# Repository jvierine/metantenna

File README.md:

# Open antenna designs

**TL;DR:** Open-source antenna hardware designs aimed at high performance. We hope anyone can take a design, make the changes they need, and have the boards assembled by a turn-key manufacturer.

| Design | Intended use | Status |
| --- | --- | --- |
| [VHF meteor-radar antenna](vhf/) | Crossed dipoles, independent X/Y outputs; 30–55 MHz electronics, arm lengths selected for the radar frequency | Engineering prototype; modeled sensitivity and fabrication files available |
| [HF active antenna](hf/) | Balanced high-impedance input; nominal 0.1–30 MHz | Development prototype; sensitivity and linearity not yet qualified |

Both designs use 50 Ω coax outputs, a 12 V bias tee and common-mode filtering. The HF input architecture differs from the approximately 50 Ω VHF input.

[VHF single-sided manufacturing variant](variants/vhf-jlc/)

## SURTR · VHF meteor radar

**Specular-scatter Unit for Receiving Trail Returns**

[SURTR antenna head with centered SMA connectors](variants/vhf-jlc-center/)

**VHF indoor bias tee — power injection and filtering at the receiver.**

## HF example

**HF indoor bias tee — separate low-frequency common-mode filtering.**

The design folders contain the schematics, PCB layouts, simulation results and manufacturing guidance. Shared [mechanical designs](mechanical/), [modeling code](simulation/) and [CAD generators](hardware/) are kept at the repository root.

[NEC impedance models](models/nec/) cover 1 m, 1.5 m and 2 m arms from 0.1 to 150 MHz in 0.05 MHz steps, with complex X/Y feedpoint impedance in HDF5.

These are open engineering prototypes, not certified products. Simulation and CAD checks do not replace RF measurements of assembled boards. No manufacturing order has been placed. The five-set VHF electronics budget is $70–100 per set including the bias tee, excluding coax, mast, enclosure, tax and shipping; this is an estimate, not a supplier quote.

## KiCad version for collaboration

Use **KiCad 10.0.x stable** for these designs. Nico uses 10.0.5; local validation used 10.0.8. KiCad documents point releases as file-compatible. Avoid saving shared files with a newer major version or a nightly build until the team agrees to migrate. Project-local symbols and footprints are included; retain `sym-lib-table`, `fp-lib-table` and the adjacent library directories when copying a design.

`main` is the integrated working version: VHF and HF designs, retained common-mode filtering, and Nico's reviewed VHF hierarchy/coupling updates. `pfeffer-review` remains Nico's review branch.

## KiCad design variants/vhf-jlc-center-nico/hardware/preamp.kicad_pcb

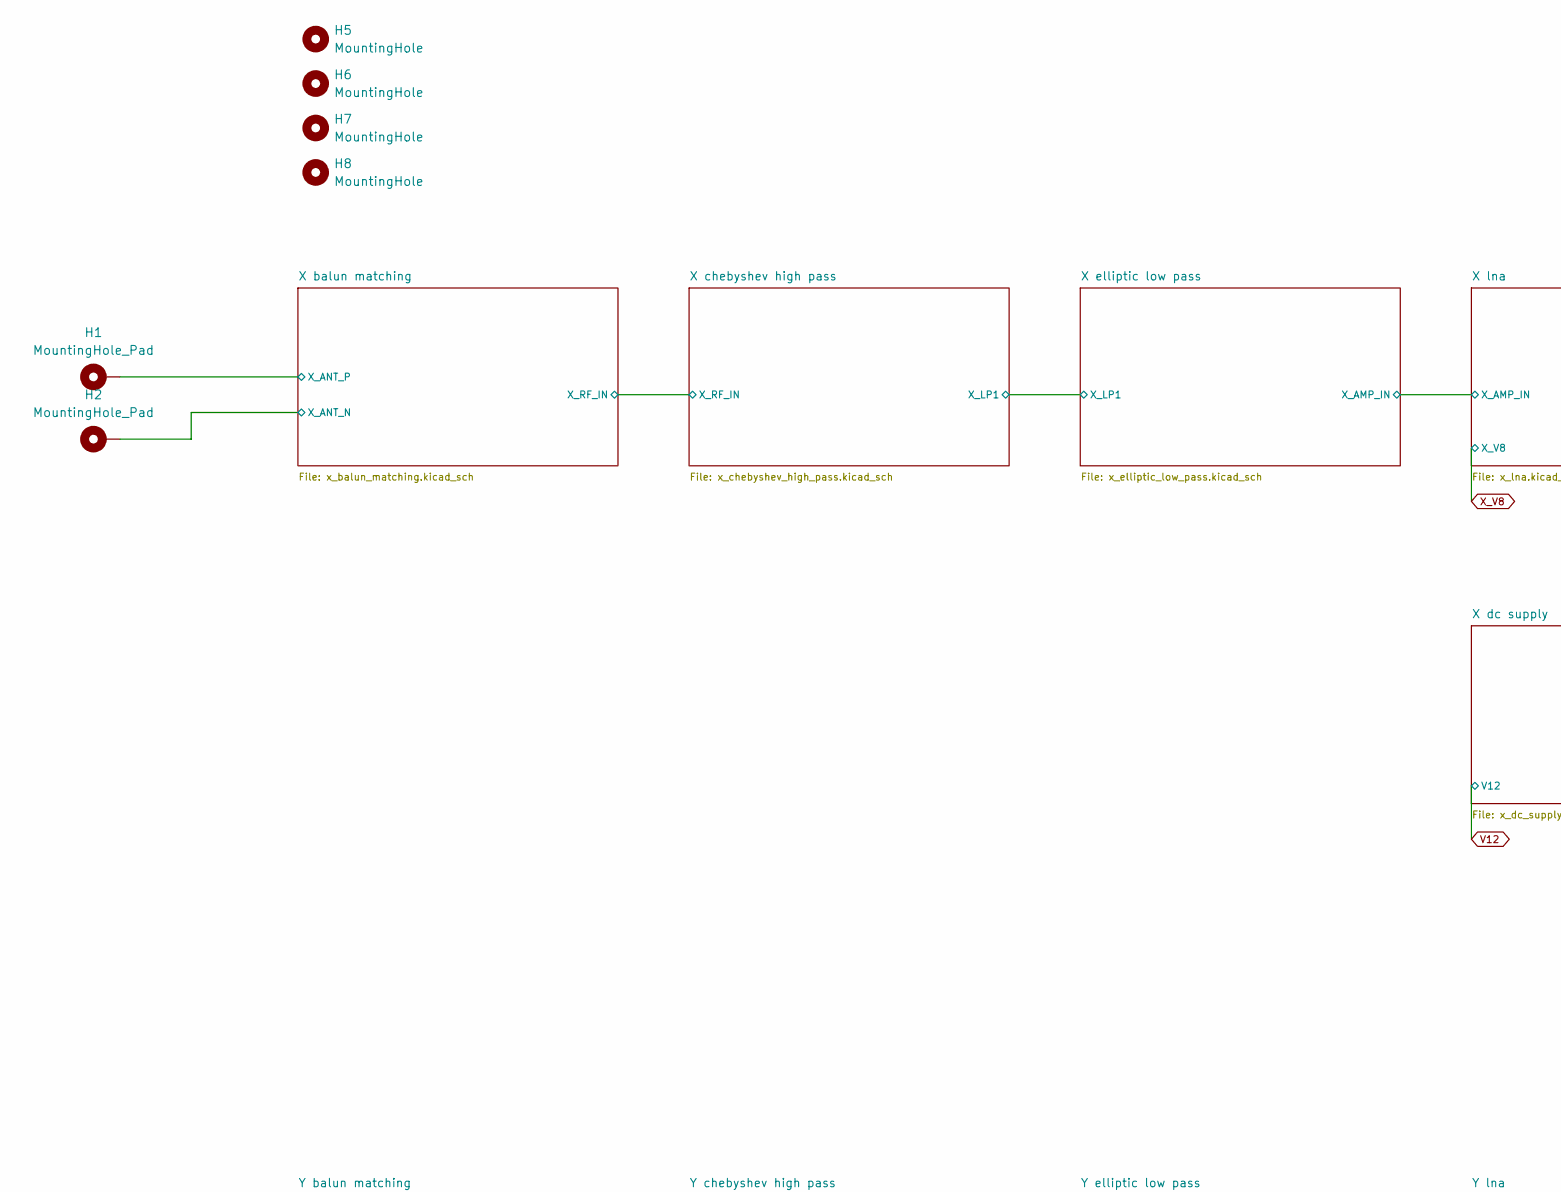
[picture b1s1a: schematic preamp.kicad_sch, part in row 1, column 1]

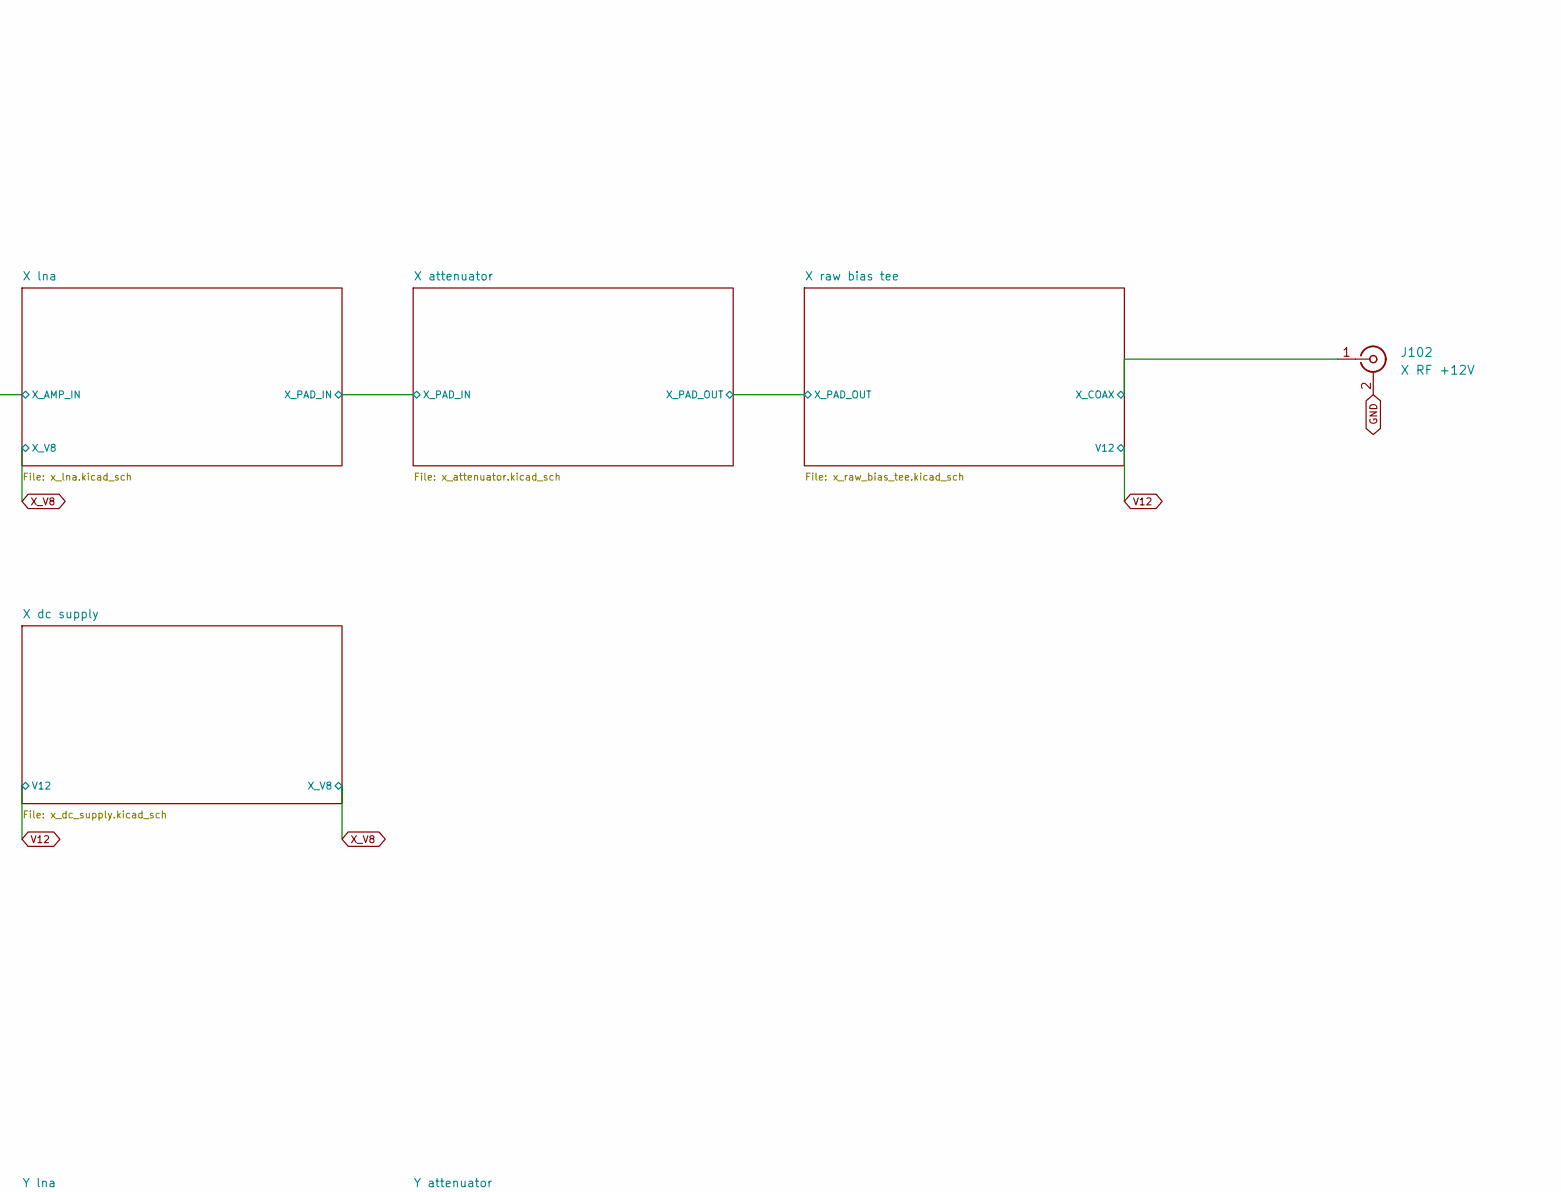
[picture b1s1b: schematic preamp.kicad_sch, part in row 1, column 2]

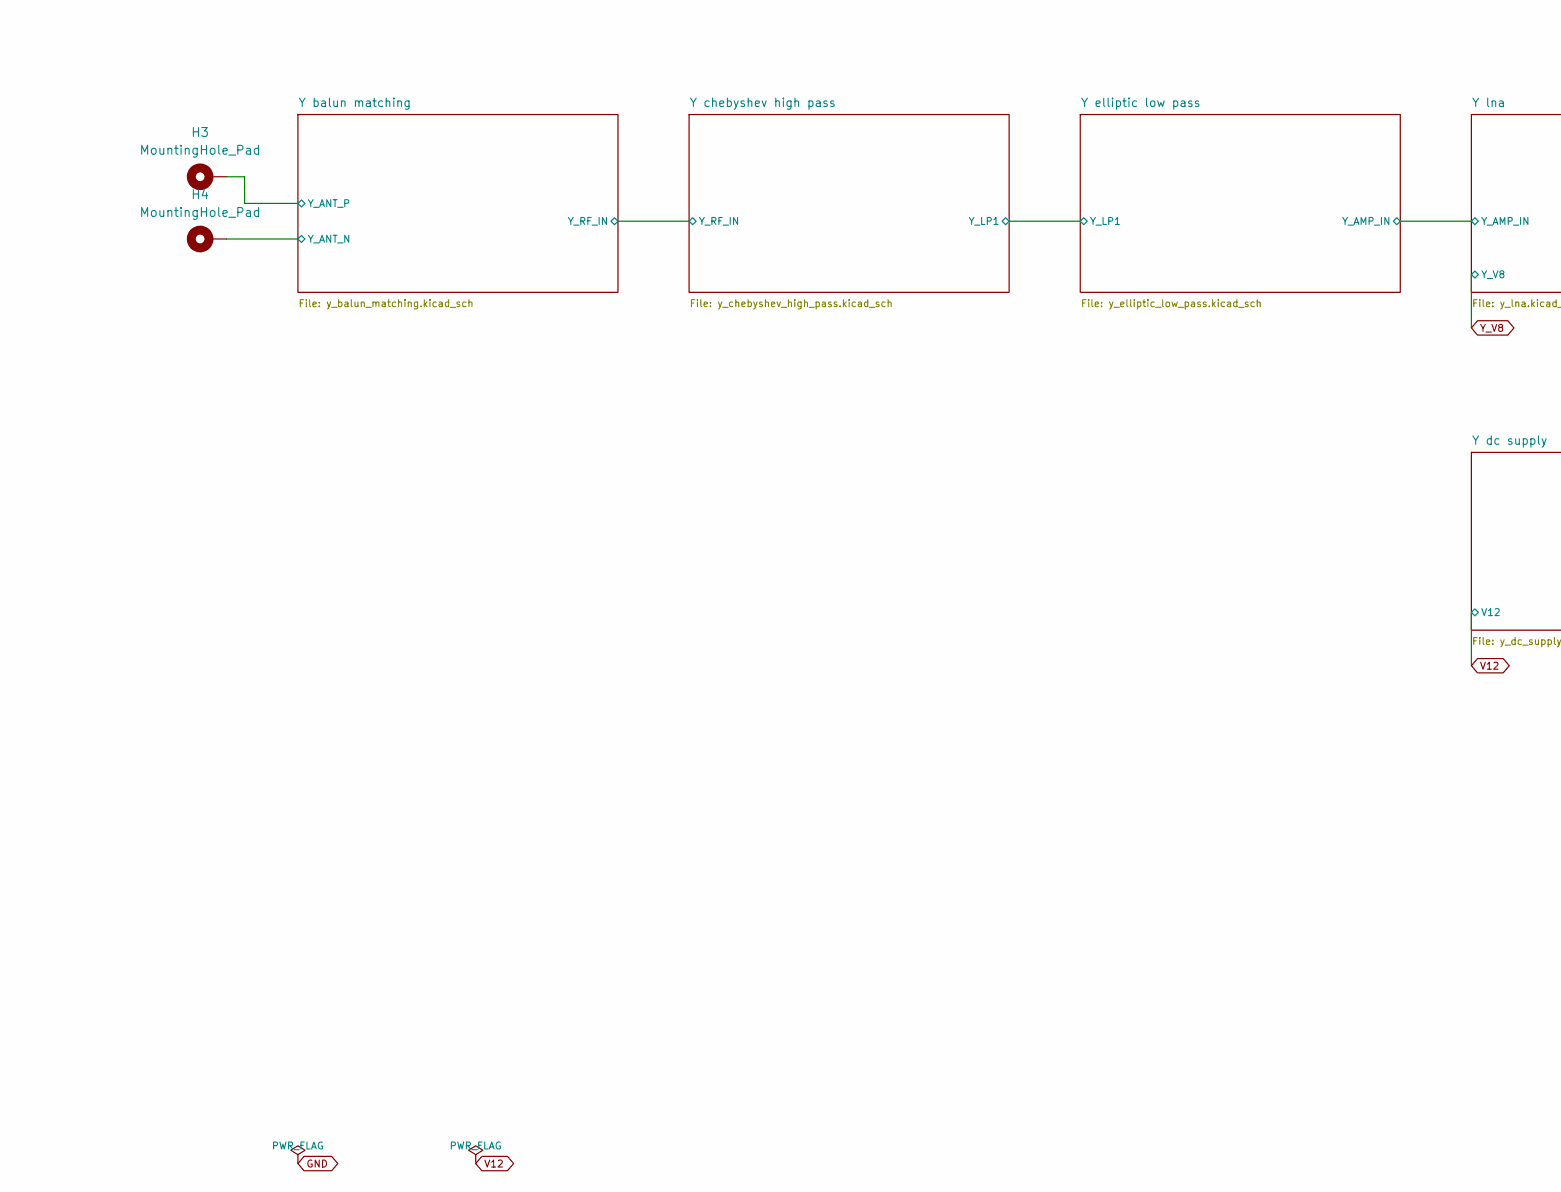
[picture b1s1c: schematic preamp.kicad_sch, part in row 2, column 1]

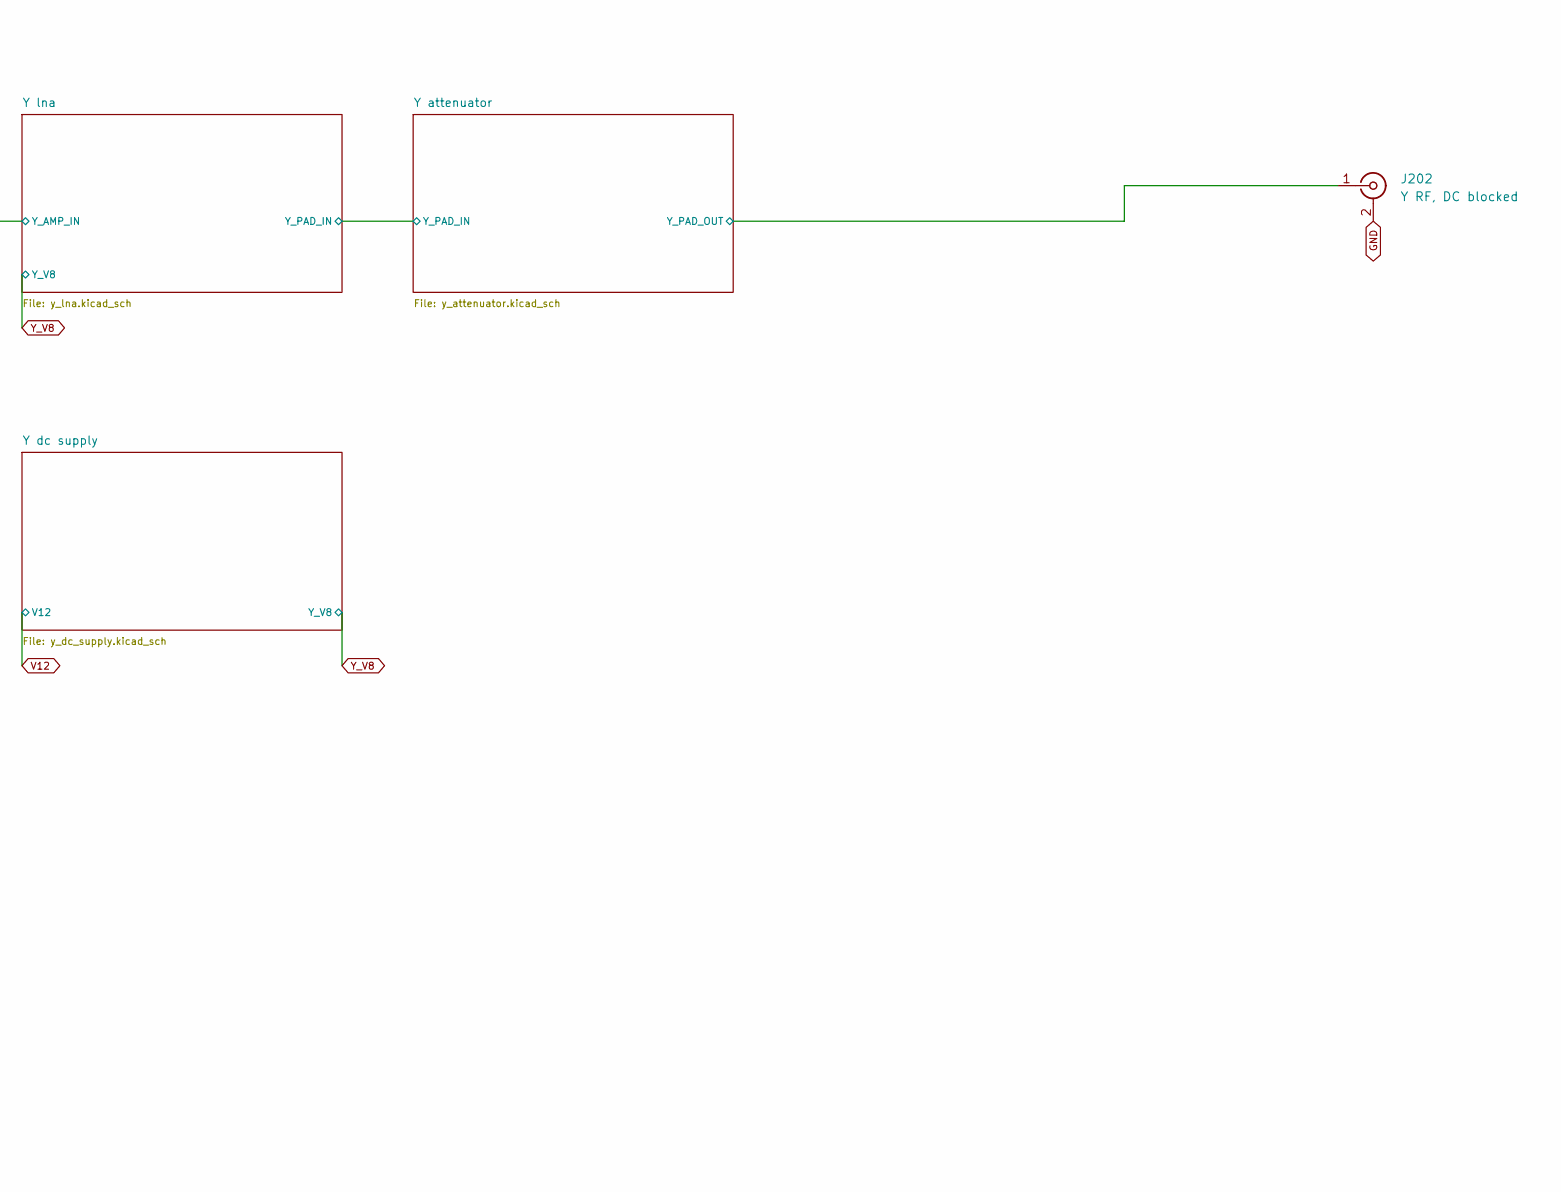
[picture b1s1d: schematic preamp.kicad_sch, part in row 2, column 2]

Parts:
H1, H2, H3, H4: MountingHole_Pad; MountingHole_3.2mm_M3_Pad_Via
H5, H6, H7, H8: MountingHole; MountingHole_3.2mm_M3_Pad_Via
J102: X RF +12V; SMA_Amphenol_132134-11_Vertical; MPN SMA-KE-347A-H13.5-P
J202: Y RF, DC blocked; SMA_Amphenol_132134-11_Vertical; MPN SMA-KE-347A-H13.5-P

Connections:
GND: J102.2 (Ext), J202.2 (Ext); also elsewhere on the board
X_ANT_N: H2.1 (1_1); also elsewhere on the board
X_ANT_P: H1.1 (1_1); also elsewhere on the board
X_COAX: J102.1 (In); also elsewhere on the board
Y_ANT_N: H4.1 (1_1); also elsewhere on the board
Y_ANT_P: H3.1 (1_1); also elsewhere on the board
Y_PAD_OUT: J202.1 (In); also elsewhere on the board

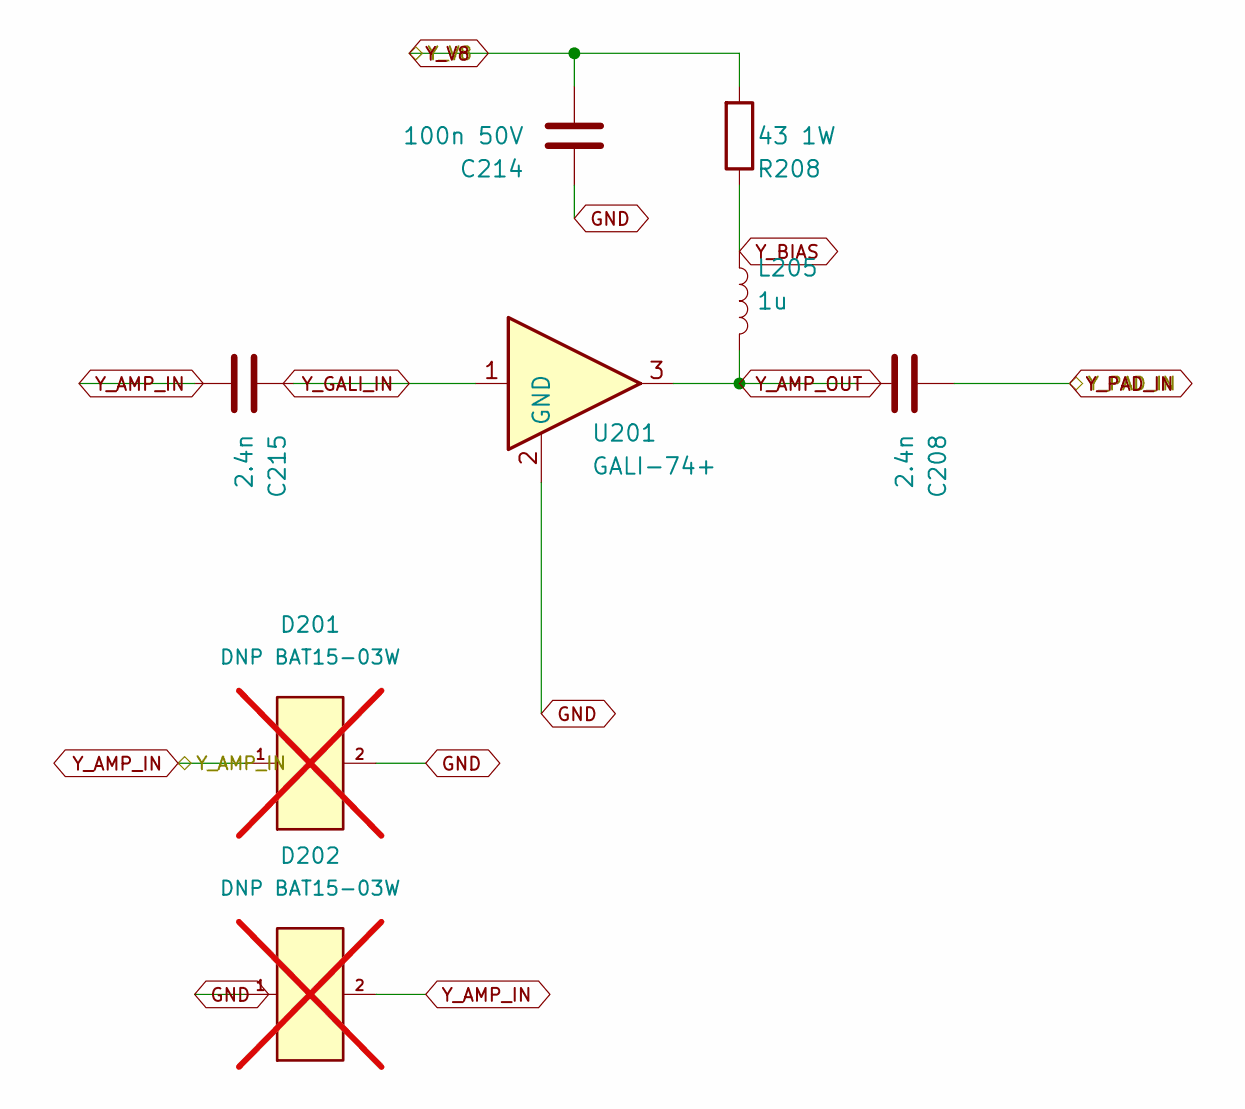
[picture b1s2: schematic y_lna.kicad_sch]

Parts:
C208, C215: 2.4n; C_0805_2012Metric; MPN GRM2165C1H242JA01D
C214: 100n 50V; C_0805_2012Metric; MPN GRM21BR71H104KA01L
D201, D202: DNP BAT15-03W; SOD323; MPN BAT15-03W; not fitted
L205: 1u; L_1008_2520Metric; MPN AHW2520C-1R0JTF
R208: 43 1W; R_2512_6332Metric; MPN 25121WF430JT4E
U201: GALI-74+; SOT-89-3; MPN GALI-74+

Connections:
GND: C214.2, D201.2, D202.1, U201.2 (GND_2); also elsewhere on the board
Y_AMP_IN: C215.1, D201.1, D202.2; also elsewhere on the board
Y_AMP_OUT: C208.1, L205.2, U201.3
Y_BIAS: L205.1, R208.2
Y_GALI_IN: C215.2, U201.1
Y_PAD_IN: C208.2; also elsewhere on the board
Y_V8: C214.1, R208.1; also elsewhere on the board

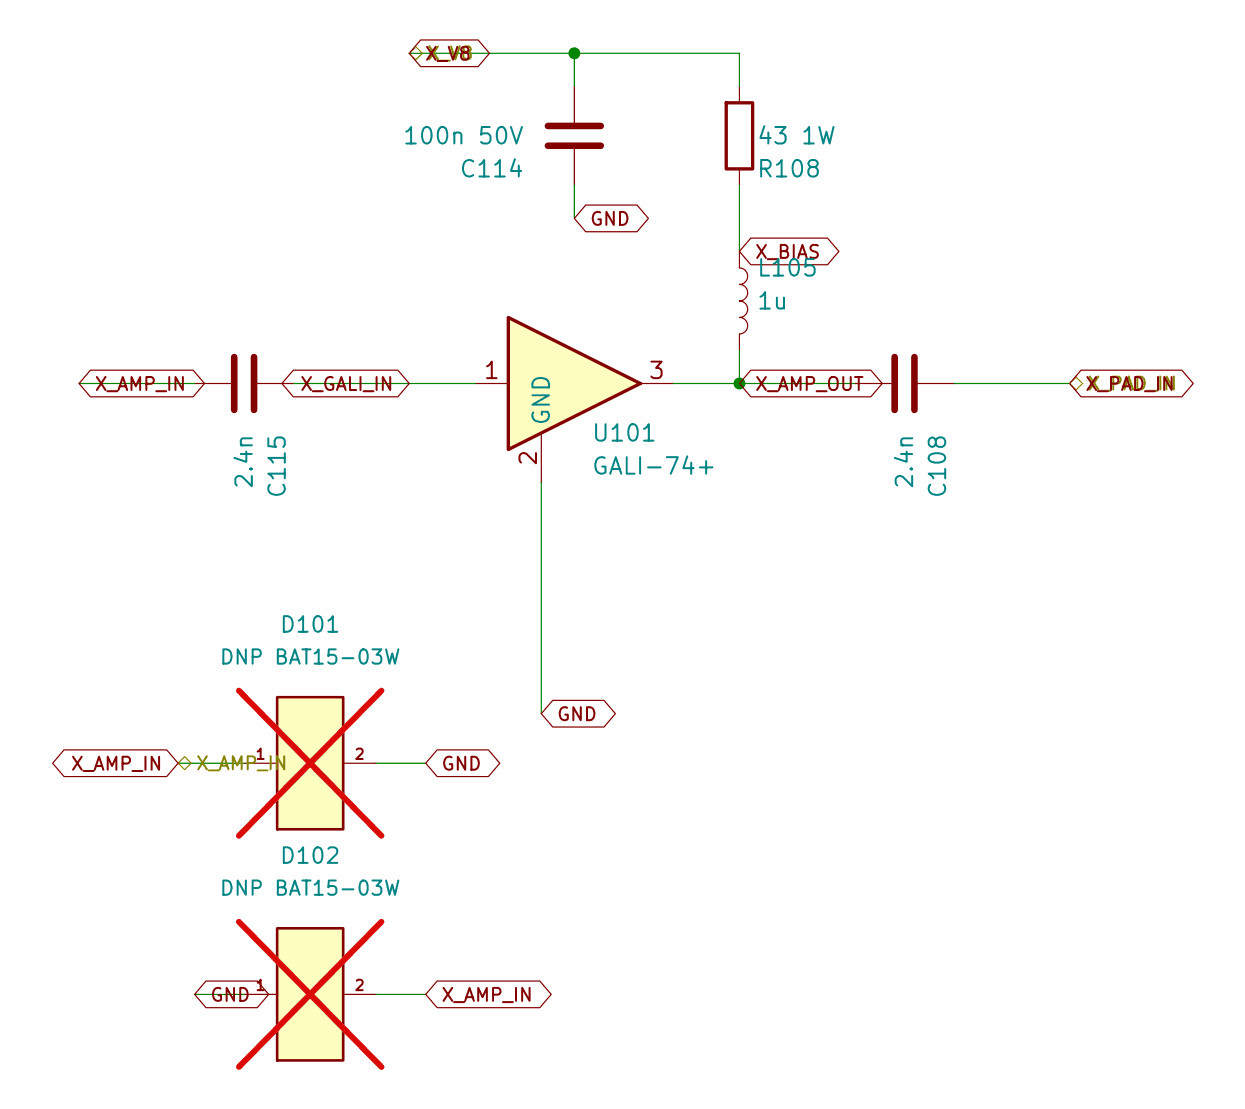
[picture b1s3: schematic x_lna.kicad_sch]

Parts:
C108, C115: 2.4n; C_0805_2012Metric; MPN GRM2165C1H242JA01D
C114: 100n 50V; C_0805_2012Metric; MPN GRM21BR71H104KA01L
D101, D102: DNP BAT15-03W; SOD323; MPN BAT15-03W; not fitted
L105: 1u; L_1008_2520Metric; MPN AHW2520C-1R0JTF
R108: 43 1W; R_2512_6332Metric; MPN 25121WF430JT4E
U101: GALI-74+; SOT-89-3; MPN GALI-74+

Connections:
GND: C114.2, D101.2, D102.1, U101.2 (GND_2); also elsewhere on the board
X_AMP_IN: C115.1, D101.1, D102.2; also elsewhere on the board
X_AMP_OUT: C108.1, L105.2, U101.3
X_BIAS: L105.1, R108.2
X_GALI_IN: C115.2, U101.1
X_PAD_IN: C108.2; also elsewhere on the board
X_V8: C114.1, R108.1; also elsewhere on the board

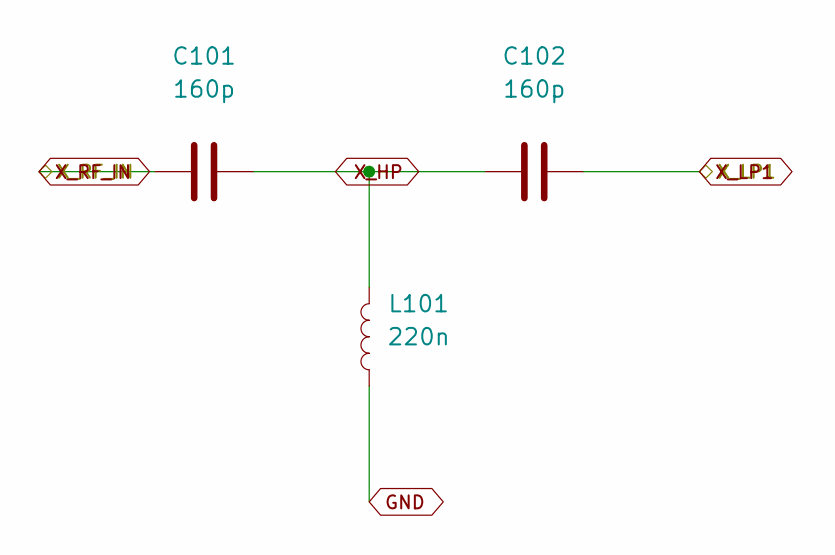
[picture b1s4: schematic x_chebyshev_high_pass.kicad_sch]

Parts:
C101, C102: 160p; C_0805_2012Metric; MPN 0805N161J500CT
L101: 220n; L_0805_2012Metric; MPN 0805HP-221XGRC

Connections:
GND: L101.2 (1); also elsewhere on the board
X_HP: C101.2, C102.1, L101.1 (2)
X_LP1: C102.2; also elsewhere on the board
X_RF_IN: C101.1; also elsewhere on the board

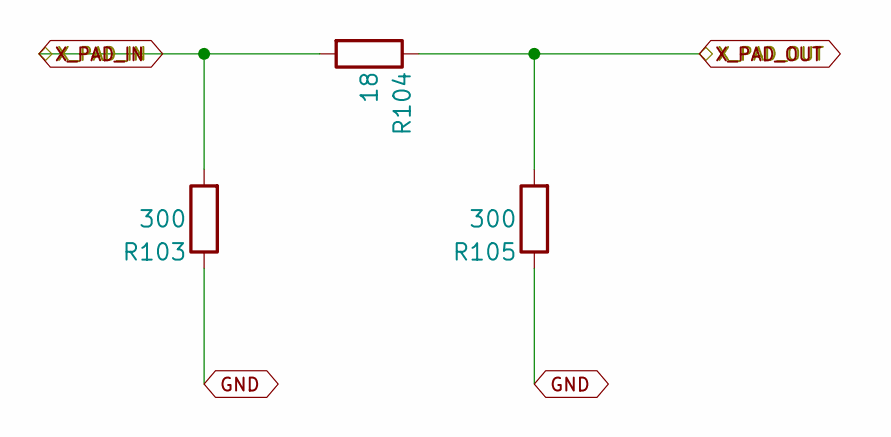
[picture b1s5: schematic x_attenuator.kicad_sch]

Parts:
R103, R105: 300; R_0805_2012Metric; MPN RC0805FR-07300RL
R104: 18; R_0805_2012Metric; MPN RC0805FR-0718RL

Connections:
GND: R103.2, R105.2; also elsewhere on the board
X_PAD_IN: R103.1, R104.1; also elsewhere on the board
X_PAD_OUT: R104.2, R105.1; also elsewhere on the board

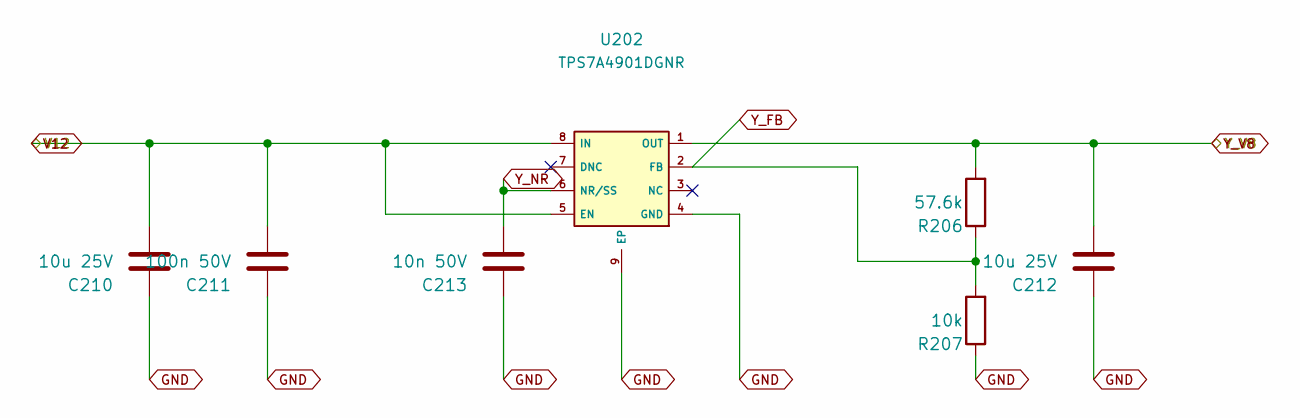
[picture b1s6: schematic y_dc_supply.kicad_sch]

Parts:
C210, C212: 10u 25V; C_1206_3216Metric; MPN GRM31CR61E106KA12L
C211: 100n 50V; C_0805_2012Metric; MPN GRM21BR71H104KA01L
C213: 10n 50V; C_0805_2012Metric; MPN GRM21BR71H103KA01L
R206: 57.6k; R_0805_2012Metric; MPN FRC0805F5762TS
R207: 10k; R_0805_2012Metric; MPN 0805W8F1002T5E
U202: TPS7A4901DGNR; HVSSOP-8-1EP_3x3mm_P0.65mm_EP1.57x1.89mm_ThermalVias; MPN TPS7A4901DGNR

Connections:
GND: C210.2, C211.2, C212.2, C213.2, R207.2, U202.4 (GND), U202.9 (EP); also elsewhere on the board
V12: C210.1, C211.1, U202.5 (EN), U202.8 (IN); also elsewhere on the board
Y_FB: R206.2, R207.1, U202.2 (FB)
Y_NR: C213.1, U202.6 (NR/SS)
Y_V8: C212.1, R206.1, U202.1 (OUT); also elsewhere on the board

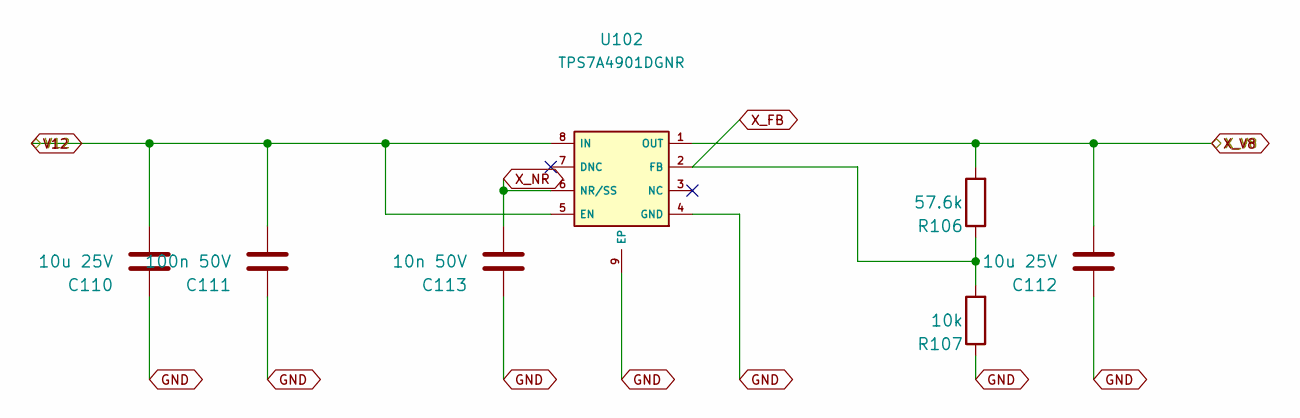
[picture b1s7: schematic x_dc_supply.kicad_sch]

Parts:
C110, C112: 10u 25V; C_1206_3216Metric; MPN GRM31CR61E106KA12L
C111: 100n 50V; C_0805_2012Metric; MPN GRM21BR71H104KA01L
C113: 10n 50V; C_0805_2012Metric; MPN GRM21BR71H103KA01L
R106: 57.6k; R_0805_2012Metric; MPN FRC0805F5762TS
R107: 10k; R_0805_2012Metric; MPN 0805W8F1002T5E
U102: TPS7A4901DGNR; HVSSOP-8-1EP_3x3mm_P0.65mm_EP1.57x1.89mm_ThermalVias; MPN TPS7A4901DGNR

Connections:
GND: C110.2, C111.2, C112.2, C113.2, R107.2, U102.4 (GND), U102.9 (EP); also elsewhere on the board
V12: C110.1, C111.1, U102.5 (EN), U102.8 (IN); also elsewhere on the board
X_FB: R106.2, R107.1, U102.2 (FB)
X_NR: C113.1, U102.6 (NR/SS)
X_V8: C112.1, R106.1, U102.1 (OUT); also elsewhere on the board

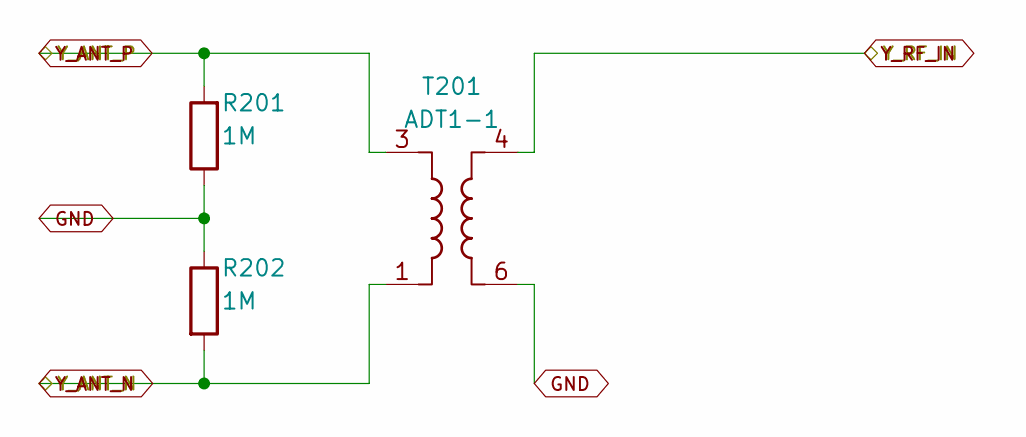
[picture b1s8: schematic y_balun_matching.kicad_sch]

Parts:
R201, R202: 1M; R_0805_2012Metric; MPN 0805W8F1004T5E
T201: ADT1-1; Mini-Circuits_CD542_H2.84mm

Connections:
GND: R201.2, R202.2, T201.6; also elsewhere on the board
Y_ANT_N: R202.1, T201.1; also elsewhere on the board
Y_ANT_P: R201.1, T201.3; also elsewhere on the board
Y_RF_IN: T201.4; also elsewhere on the board

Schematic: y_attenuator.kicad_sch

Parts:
R203, R205: 300; R_0805_2012Metric; MPN RC0805FR-07300RL
R204: 18; R_0805_2012Metric; MPN RC0805FR-0718RL

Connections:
GND: R203.2, R205.2; also elsewhere on the board
Y_PAD_IN: R203.1, R204.1; also elsewhere on the board
Y_PAD_OUT: R204.2, R205.1; also elsewhere on the board

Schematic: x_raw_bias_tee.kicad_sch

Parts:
C109: 1n; C_0805_2012Metric; MPN CGA4F3C0G2E102JT0Y0N
D103: SS14; SMA_DIODE; MPN SS14; not fitted
D104: SMAJ15A; SMA_DIODE; MPN SMAJ15A; not fitted
L104: 1u; L_1008_2520Metric; MPN AHW2520C-1R0JTF

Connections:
V12: D103.1, D104.1, L104.2 (1); also elsewhere on the board
X_COAX: C109.2, L104.1 (2); also elsewhere on the board
X_PAD_OUT: C109.1; also elsewhere on the board

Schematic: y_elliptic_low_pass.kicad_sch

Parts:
C203: 36p; C_0805_2012Metric; MPN TCC0805COG360J500BT
C204: 33p; C_0805_2012Metric; MPN CC0805JRNPO9BN330
C205: 75p; C_0805_2012Metric; MPN GQM2195C2E750JB12D
C206: 20p; C_0805_2012Metric; MPN CL21C200JBANNNC
C207: 43p; C_0805_2012Metric; MPN CC0805JRNPO9BN430
L202: 100n; L_0805_2012Metric; MPN AHW2012C-R10JTF
L203: 120n; L_0805_2012Metric; MPN 0805HP-121XGRC

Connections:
GND: C203.2, C205.2, C207.2; also elsewhere on the board
Y_AMP_IN: C206.2, C207.1, L203.2 (1); also elsewhere on the board
Y_LP1: C203.1, C204.1, L202.1 (2); also elsewhere on the board
Y_LP2: C204.2, C205.1, C206.1, L202.2 (1), L203.1 (2)

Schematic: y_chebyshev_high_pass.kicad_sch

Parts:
C201, C202: 160p; C_0805_2012Metric; MPN 0805N161J500CT
L201: 220n; L_0805_2012Metric; MPN 0805HP-221XGRC

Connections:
GND: L201.2 (1); also elsewhere on the board
Y_HP: C201.2, C202.1, L201.1 (2)
Y_LP1: C202.2; also elsewhere on the board
Y_RF_IN: C201.1; also elsewhere on the board

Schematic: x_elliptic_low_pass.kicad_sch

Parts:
C103: 36p; C_0805_2012Metric; MPN TCC0805COG360J500BT
C104: 33p; C_0805_2012Metric; MPN CC0805JRNPO9BN330
C105: 75p; C_0805_2012Metric; MPN GQM2195C2E750JB12D
C106: 20p; C_0805_2012Metric; MPN CL21C200JBANNNC
C107: 43p; C_0805_2012Metric; MPN CC0805JRNPO9BN430
L102: 100n; L_0805_2012Metric; MPN AHW2012C-R10JTF
L103: 120n; L_0805_2012Metric; MPN 0805HP-121XGRC

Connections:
GND: C103.2, C105.2, C107.2; also elsewhere on the board
X_AMP_IN: C106.2, C107.1, L103.2 (1); also elsewhere on the board
X_LP1: C103.1, C104.1, L102.1 (2); also elsewhere on the board
X_LP2: C104.2, C105.1, C106.1, L102.2 (1), L103.1 (2)

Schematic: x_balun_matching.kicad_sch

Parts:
R101, R102: 1M; R_0805_2012Metric; MPN 0805W8F1004T5E
T101: ADT1-1; Mini-Circuits_CD542_H2.84mm

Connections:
GND: R101.2, R102.2, T101.6; also elsewhere on the board
X_ANT_N: R102.1, T101.1; also elsewhere on the board
X_ANT_P: R101.1, T101.3; also elsewhere on the board
X_RF_IN: T101.4; also elsewhere on the board

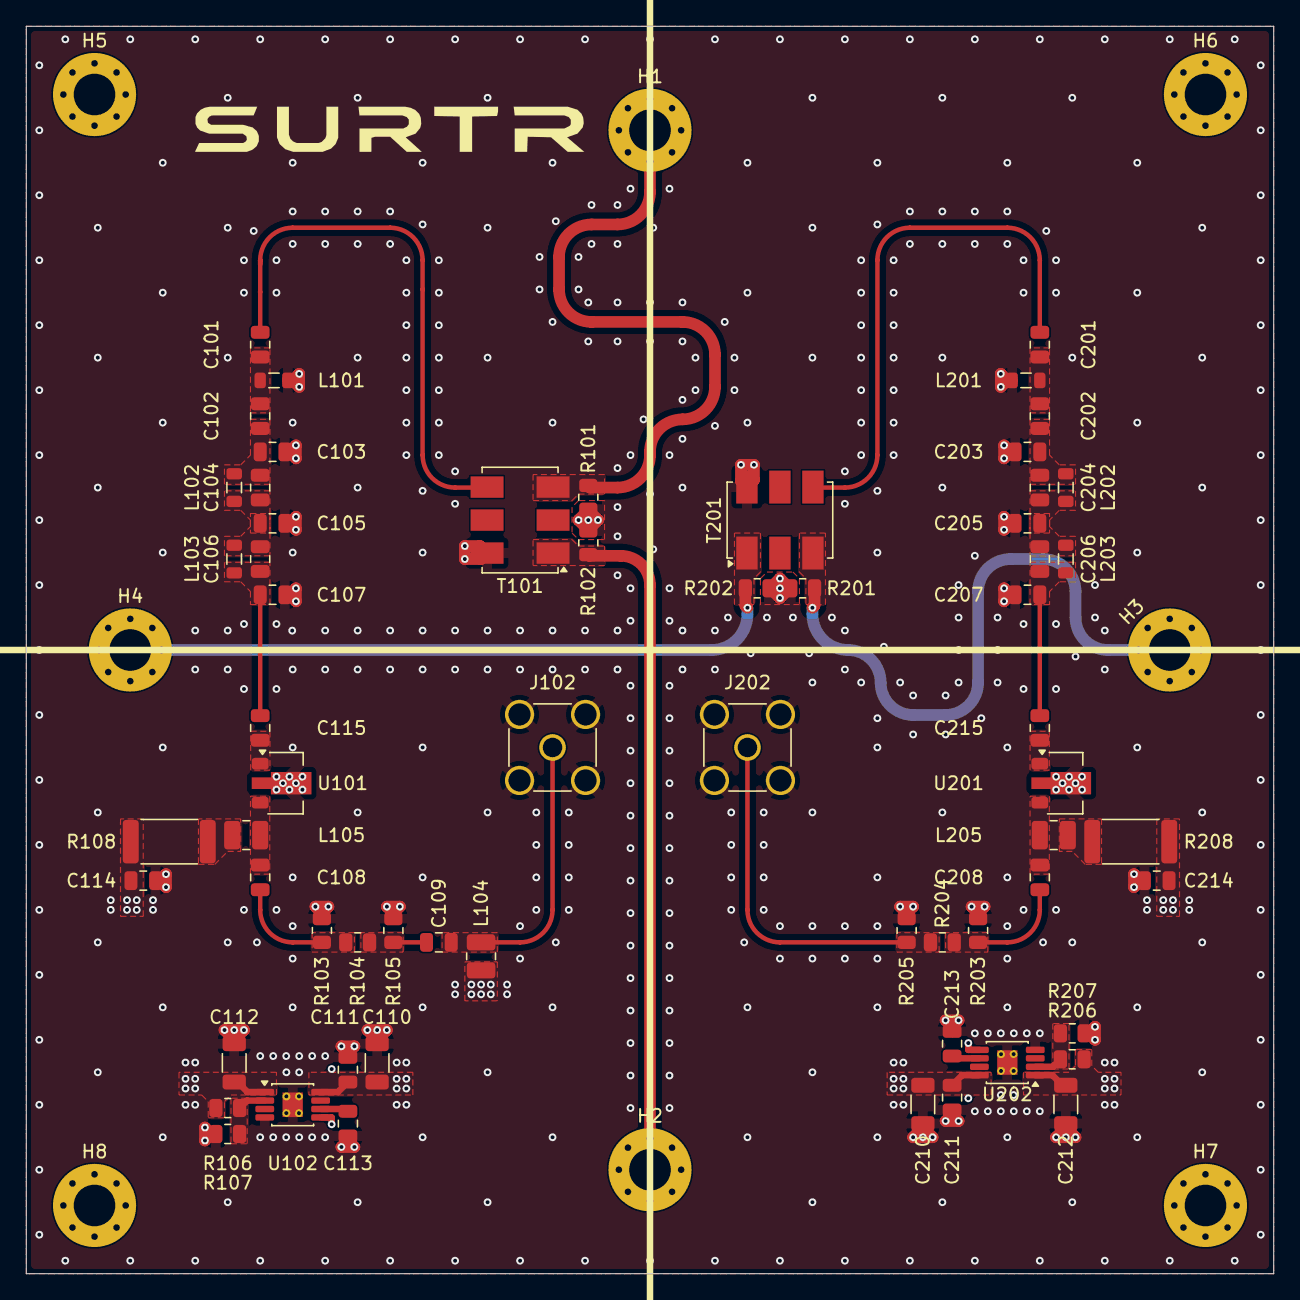
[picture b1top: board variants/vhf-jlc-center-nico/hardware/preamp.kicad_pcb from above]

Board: 4 copper layers, 96.0 x 96.0 mm, 70 parts (0 on the bottom side), 33 nets.
